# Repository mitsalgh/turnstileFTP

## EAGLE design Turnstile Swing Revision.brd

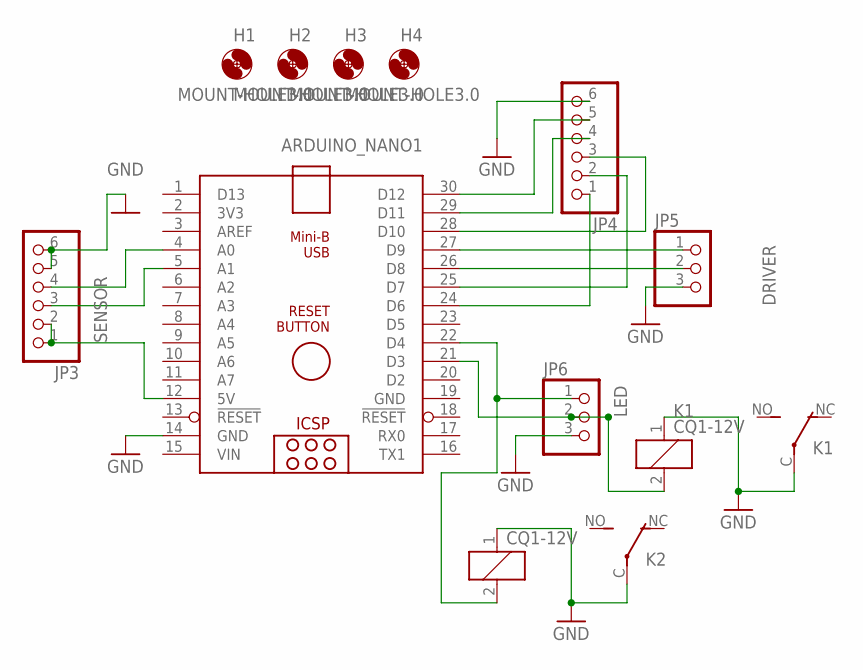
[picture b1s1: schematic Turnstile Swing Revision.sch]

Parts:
ARDUINO_NANO1: ARDUINO_NANO
H1, H2, H3, H4: MOUNT-HOLE3.0; 3,0
JP3, JP4: PINHD-1X6; 1X06
JP5, JP6: PINHD-1X3; 1X03
K1, K2: CQ1-12V; CQ1

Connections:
GND: ARDUINO_NANO1.14 (GND), ARDUINO_NANO1.19 (GND), JP3.5, JP3.6, JP4.6, JP5.3, JP6.3, K1.1, K1.C, K2.1, K2.C
unnamed: ARDUINO_NANO1.12 (5V), JP3.1, JP3.2
unnamed: ARDUINO_NANO1.5 (A1), JP3.3
unnamed: ARDUINO_NANO1.4 (A0), JP3.4
unnamed: ARDUINO_NANO1.24 (D6), JP4.1
unnamed: ARDUINO_NANO1.26 (D8), JP5.2
unnamed: ARDUINO_NANO1.27 (D9), JP5.1
unnamed: ARDUINO_NANO1.21 (D3), JP6.2, K1.2
unnamed: ARDUINO_NANO1.22 (D4), JP6.1, K2.2
unnamed: ARDUINO_NANO1.25 (D7), JP4.2
unnamed: ARDUINO_NANO1.28 (D10), JP4.3
unnamed: ARDUINO_NANO1.29 (D11), JP4.4
unnamed: ARDUINO_NANO1.30 (D12), JP4.5
VIN: ARDUINO_NANO1.15 (VIN)

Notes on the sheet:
SENSOR
LED
DRIVER

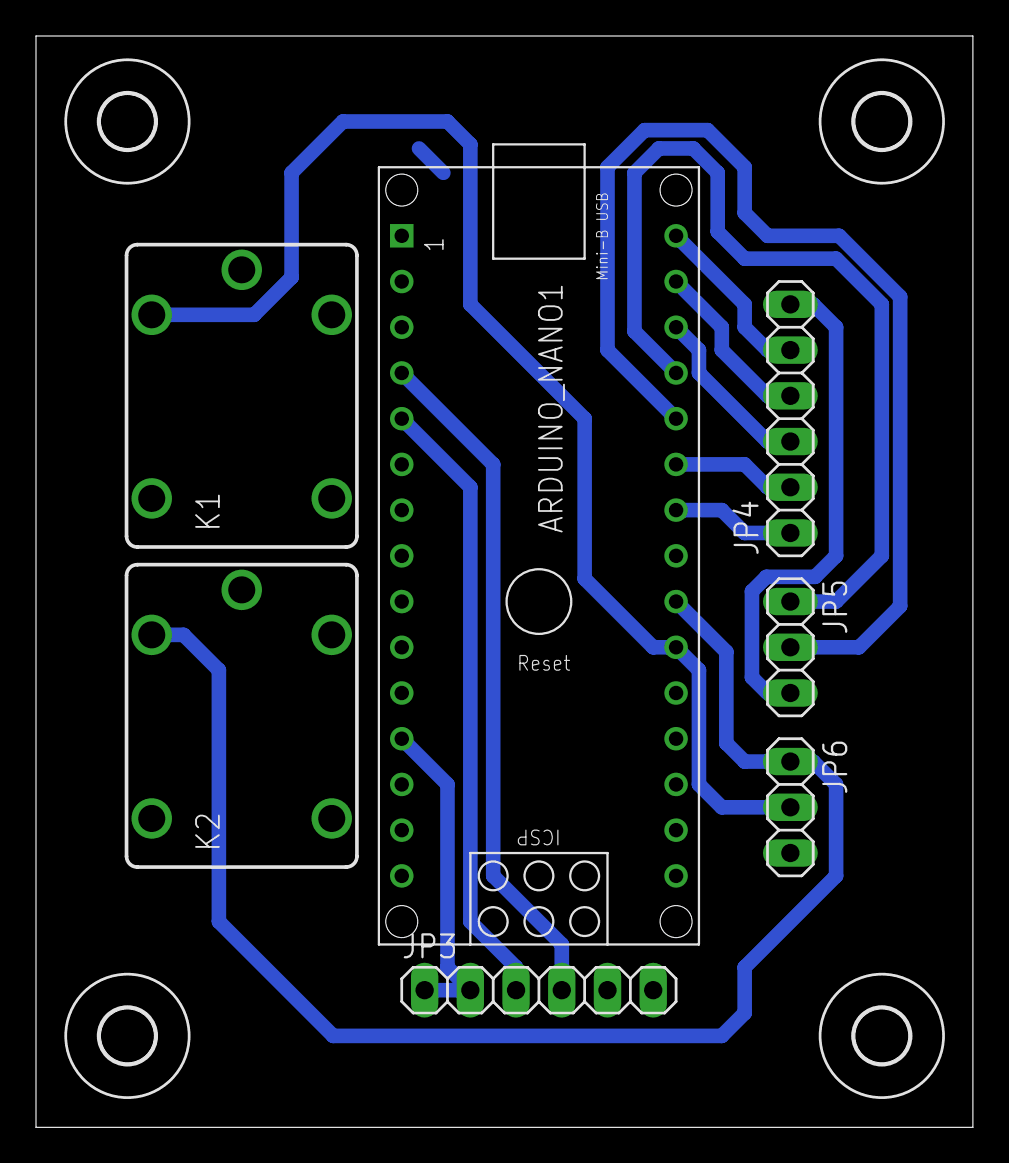
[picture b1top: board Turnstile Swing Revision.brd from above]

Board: 2 copper layers, 52.0 x 60.6 mm, 11 parts (0 on the bottom side), 13 nets.

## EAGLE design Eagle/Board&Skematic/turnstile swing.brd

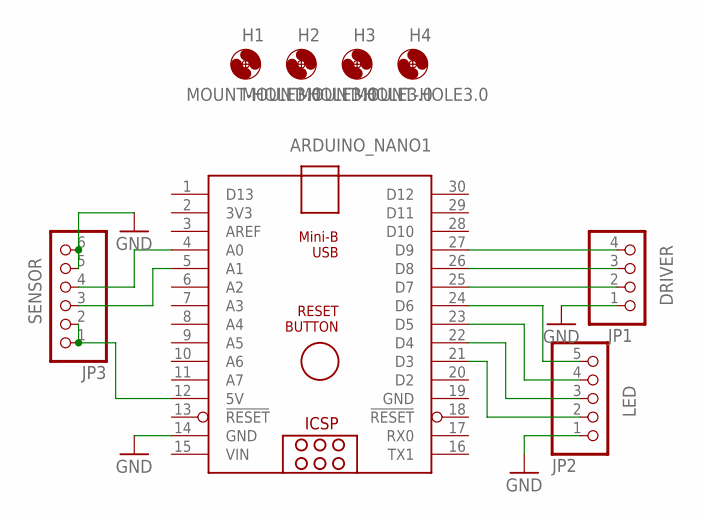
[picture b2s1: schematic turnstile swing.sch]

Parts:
ARDUINO_NANO1: ARDUINO_NANO
H1, H2, H3, H4: MOUNT-HOLE3.0; 3,0
JP1: PINHD-1X4; 1X04
JP2: PINHD-1X5; 1X05
JP3: PINHD-1X6; 1X06

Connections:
GND: ARDUINO_NANO1.14 (GND), ARDUINO_NANO1.19 (GND), JP1.1, JP2.1, JP3.5, JP3.6
unnamed: ARDUINO_NANO1.12 (5V), JP3.1, JP3.2
unnamed: ARDUINO_NANO1.5 (A1), JP3.3
unnamed: ARDUINO_NANO1.4 (A0), JP3.4
unnamed: ARDUINO_NANO1.25 (D7), JP1.2
unnamed: ARDUINO_NANO1.26 (D8), JP1.3
unnamed: ARDUINO_NANO1.27 (D9), JP1.4
unnamed: ARDUINO_NANO1.21 (D3), JP2.2
unnamed: ARDUINO_NANO1.22 (D4), JP2.3
unnamed: ARDUINO_NANO1.23 (D5), JP2.4
unnamed: ARDUINO_NANO1.24 (D6), JP2.5
VIN: ARDUINO_NANO1.15 (VIN)

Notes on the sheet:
SENSOR
LED
DRIVER

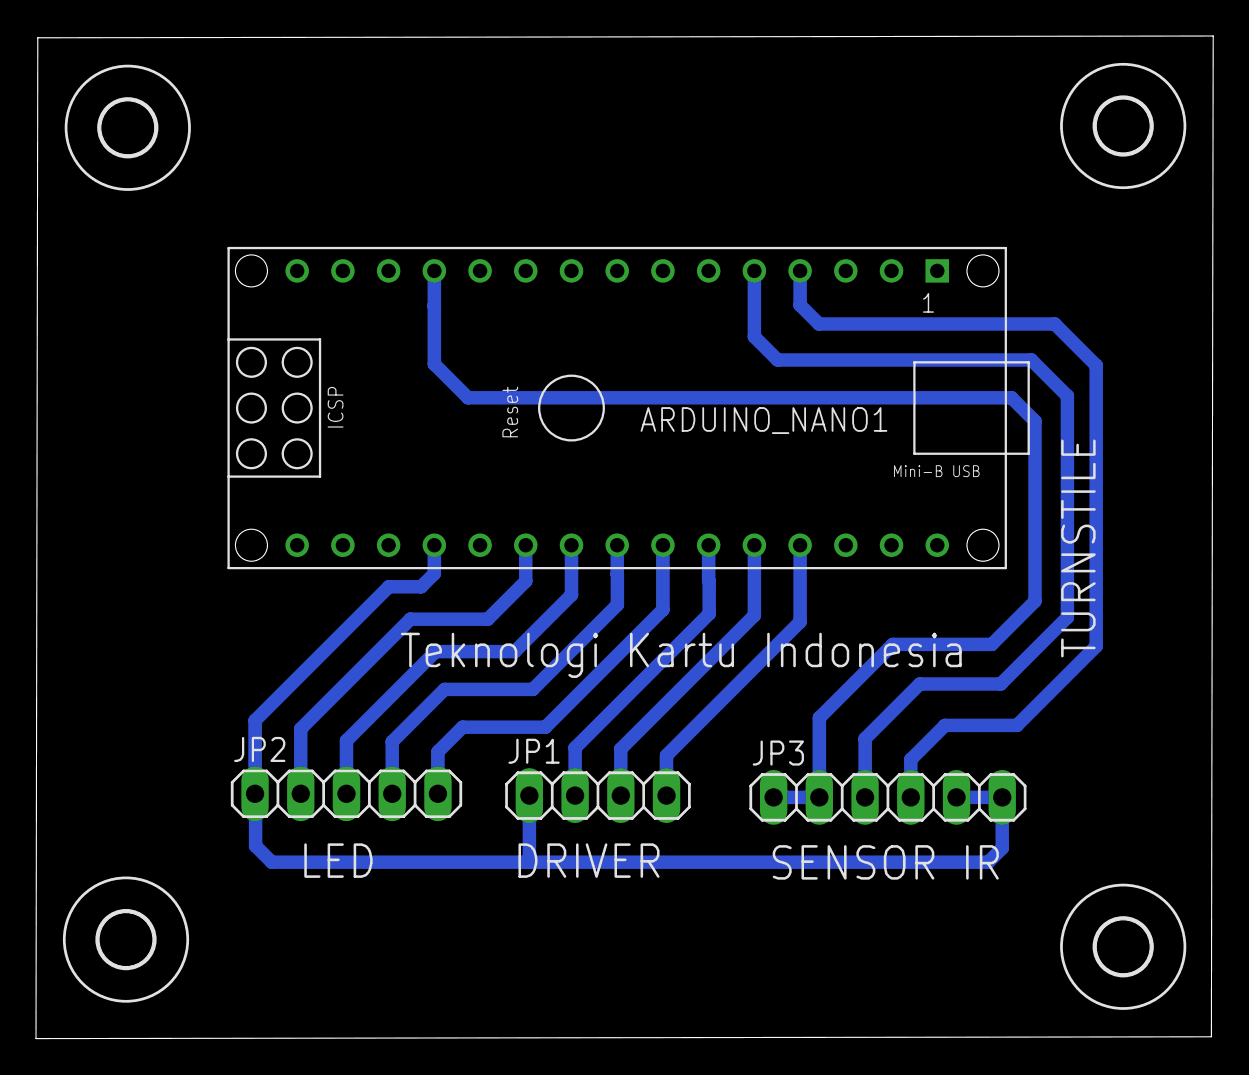
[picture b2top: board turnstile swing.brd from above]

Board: 2 copper layers, 65.4 x 55.7 mm, 8 parts (0 on the bottom side), 11 nets.

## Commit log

2024-03-01 Create Eagle
